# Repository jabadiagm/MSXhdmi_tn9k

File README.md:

# MSXhdmi_tn9k
Adaptador hdmi para MSX1

Permite conectar un MSX de primera generación a un monitor convencional. La lógica está contenida en una Tang Nano 9K que se encarga de reproducir imagen (vdp) y sonido (psg).

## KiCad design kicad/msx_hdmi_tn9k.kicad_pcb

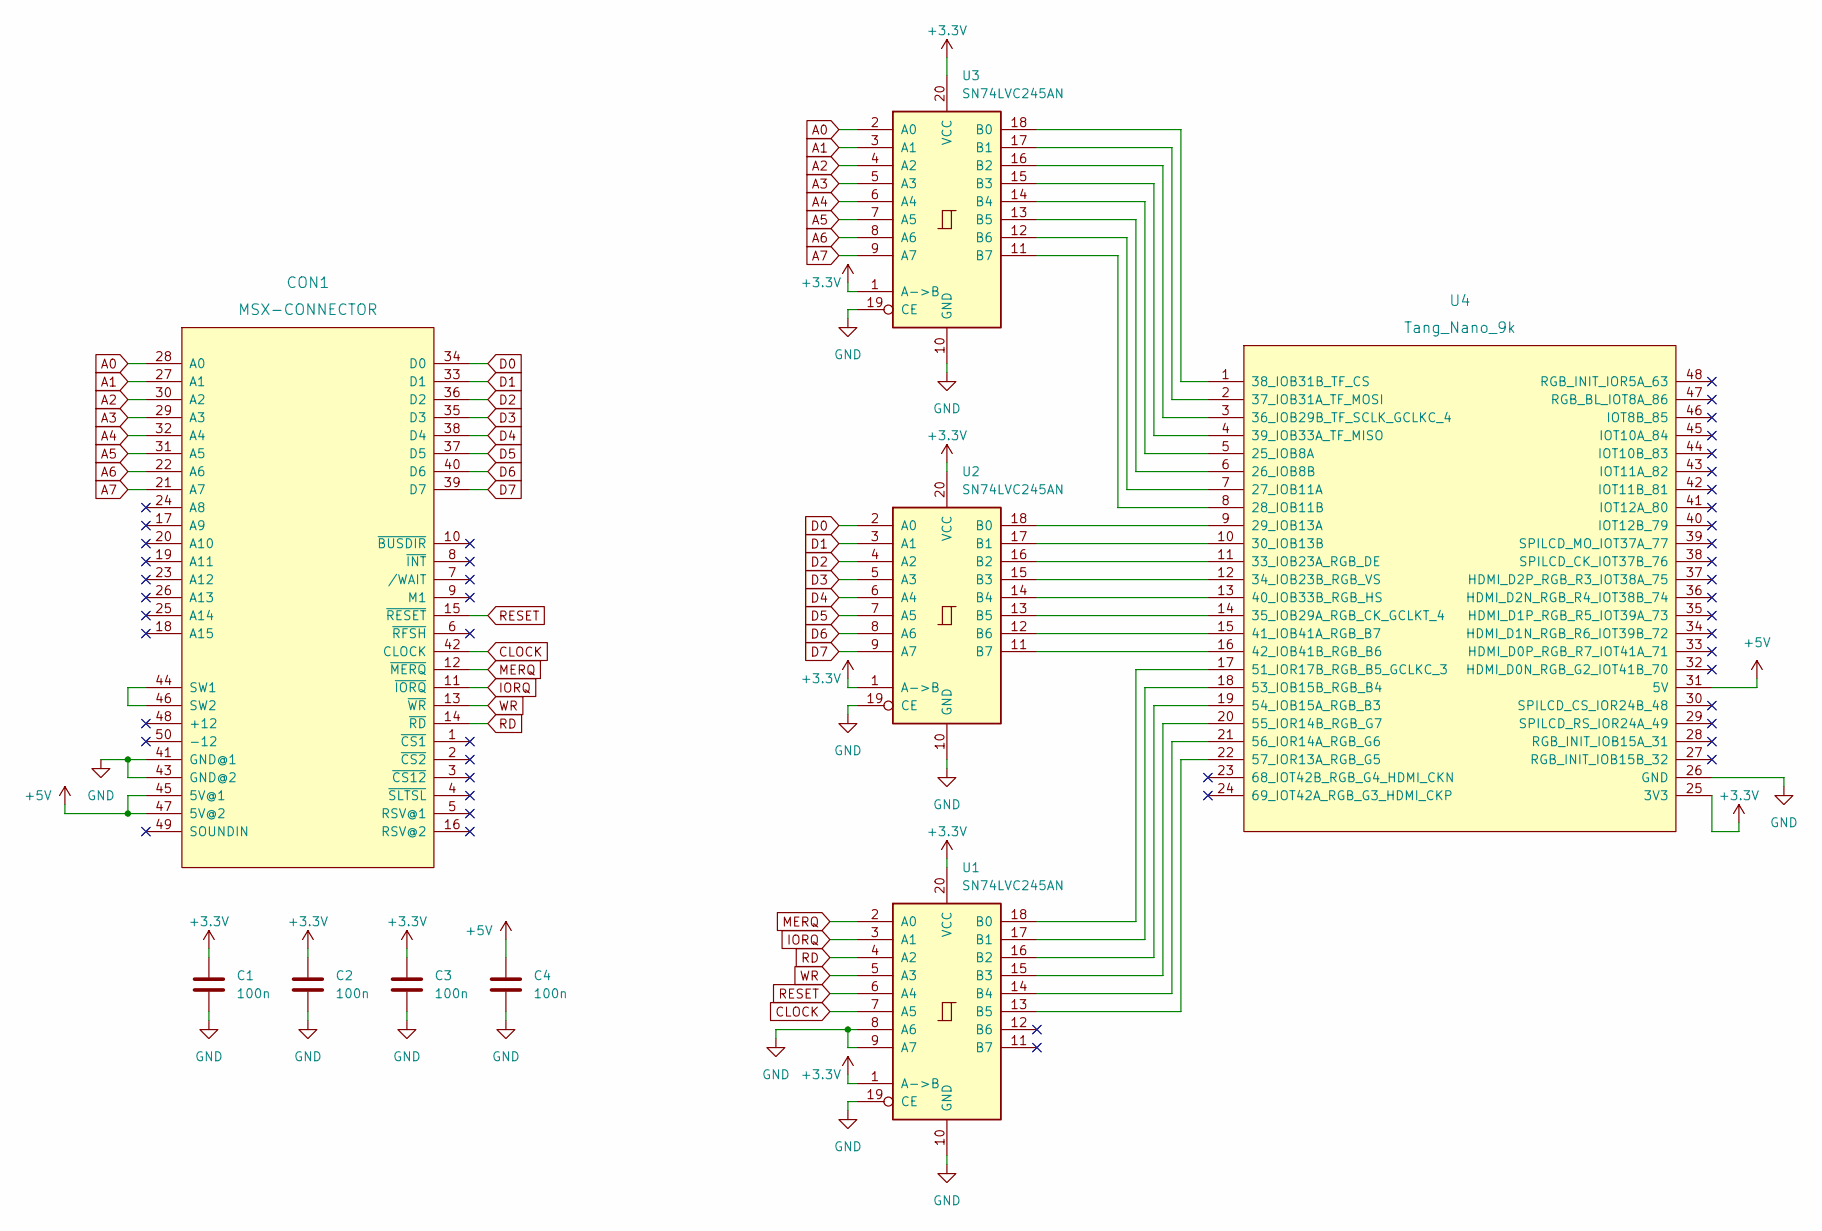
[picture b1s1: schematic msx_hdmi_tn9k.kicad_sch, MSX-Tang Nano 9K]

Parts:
C1, C2, C3, C4: 100n; C_Disc_D4.3mm_W1.9mm_P5.00mm
CON1: MSX-CONNECTOR; CARTRIDGE_MSX
U1, U2, U3: SN74LVC245AN; DIP-20_W7.62mm
U4: Tang_Nano_9k

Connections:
+3.3V: C1.1, C2.1, C3.1, U1.1 (A->B), U1.20 (VCC), U2.1 (A->B), U2.20 (VCC), U3.1 (A->B), U3.20 (VCC), U4.25 (3V3)
+5V: C4.1, CON1.45 (5V@1), CON1.47 (5V@2), U4.31 (5V)
A0: CON1.28 (A0), U3.2 (A0)
A1: CON1.27 (A1), U3.3 (A1)
A2: CON1.30 (A2), U3.4 (A2)
A3: CON1.29 (A3), U3.5 (A3)
A4: CON1.32 (A4), U3.6 (A4)
A5: CON1.31 (A5), U3.7 (A5)
A6: CON1.22 (A6), U3.8 (A6)
A7: CON1.21 (A7), U3.9 (A7)
CLOCK: CON1.42 (CLOCK), U1.7 (A5)
D0: CON1.34 (D0), U2.2 (A0)
D1: CON1.33 (D1), U2.3 (A1)
D2: CON1.36 (D2), U2.4 (A2)
D3: CON1.35 (D3), U2.5 (A3)
D4: CON1.38 (D4), U2.6 (A4)
D5: CON1.37 (D5), U2.7 (A5)
D6: CON1.40 (D6), U2.8 (A6)
D7: CON1.39 (D7), U2.9 (A7)
GND: C1.2, C2.2, C3.2, C4.2, CON1.41 (GND@1), CON1.43 (GND@2), U1.8 (A6), U1.9 (A7), U1.10 (GND), U1.19 (CE), U2.10 (GND), U2.19 (CE), U3.10 (GND), U3.19 (CE), U4.26 (GND)
IORQ: CON1.11 (~IORQ), U1.3 (A1)
MERQ: CON1.12 (~MERQ), U1.2 (A0)
unnamed: CON1.44 (SW1), CON1.46 (SW2)
unnamed: U1.13 (B5), U4.22 (57_IOR13A_RGB_G5)
unnamed: U1.14 (B4), U4.21 (56_IOR14A_RGB_G6)
unnamed: U1.15 (B3), U4.20 (55_IOR14B_RGB_G7)
unnamed: U1.16 (B2), U4.19 (54_IOB15A_RGB_B3)
unnamed: U1.17 (B1), U4.18 (53_IOB15B_RGB_B4)
unnamed: U1.18 (B0), U4.17 (51_IOR17B_RGB_B5_GCLKC_3)
unnamed: U2.11 (B7), U4.16 (42_IOB41B_RGB_B6)
unnamed: U2.12 (B6), U4.15 (41_IOB41A_RGB_B7)
unnamed: U2.13 (B5), U4.14 (35_IOB29A_RGB_CK_GCLKT_4)
unnamed: U2.14 (B4), U4.13 (40_IOB33B_RGB_HS)
unnamed: U2.15 (B3), U4.12 (34_IOB23B_RGB_VS)
unnamed: U2.16 (B2), U4.11 (33_IOB23A_RGB_DE)
unnamed: U2.17 (B1), U4.10 (30_IOB13B)
unnamed: U2.18 (B0), U4.9 (29_IOB13A)
unnamed: U3.11 (B7), U4.8 (28_IOB11B)
unnamed: U3.12 (B6), U4.7 (27_IOB11A)
unnamed: U3.13 (B5), U4.6 (26_IOB8B)
unnamed: U3.14 (B4), U4.5 (25_IOB8A)
unnamed: U3.15 (B3), U4.4 (39_IOB33A_TF_MISO)
unnamed: U3.16 (B2), U4.3 (36_IOB29B_TF_SCLK_GCLKC_4)
unnamed: U3.17 (B1), U4.2 (37_IOB31A_TF_MOSI)
unnamed: U3.18 (B0), U4.1 (38_IOB31B_TF_CS)
RD: CON1.14 (~RD), U1.4 (A2)
RESET: CON1.15 (~RESET), U1.6 (A4)
WR: CON1.13 (~WR), U1.5 (A3)

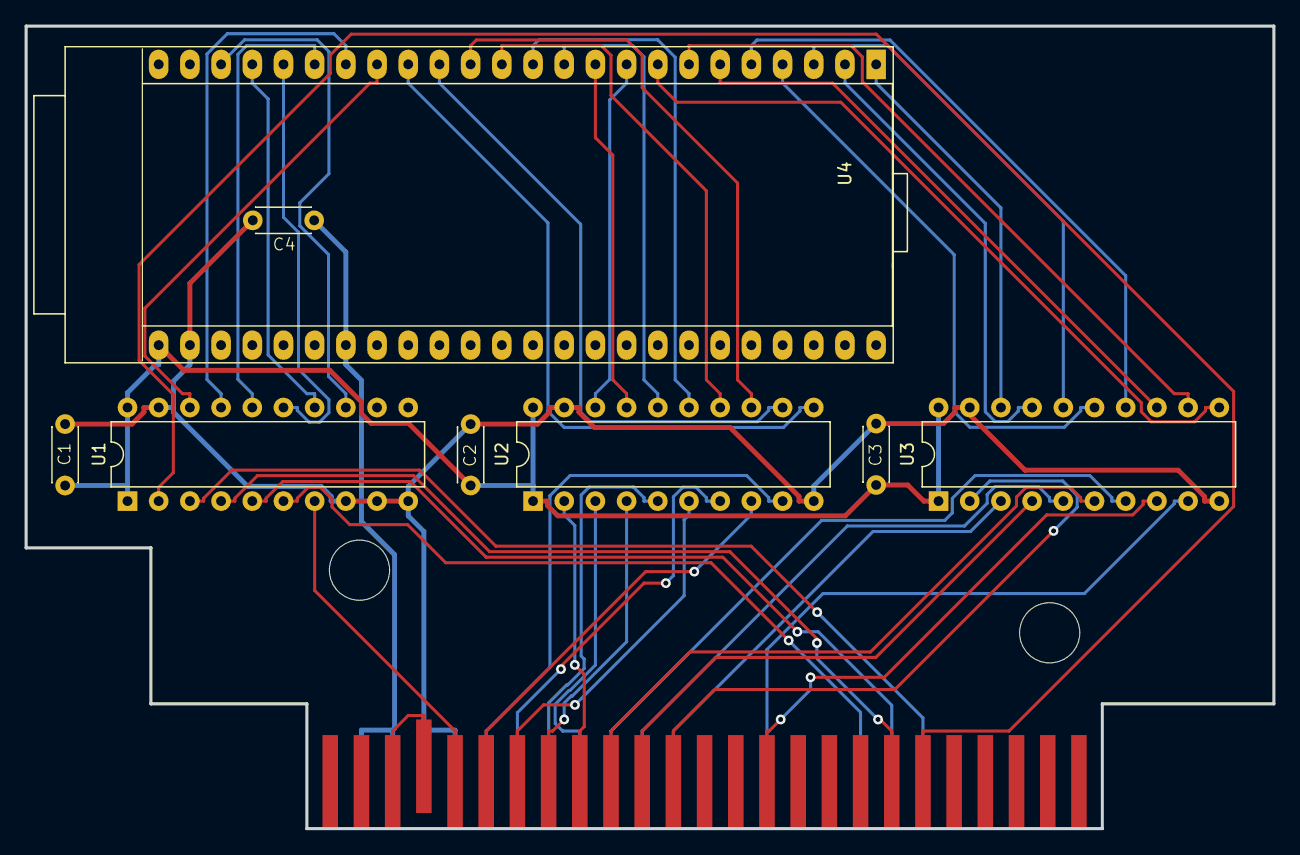
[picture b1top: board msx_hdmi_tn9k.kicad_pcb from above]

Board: 2 copper layers, 101.6 x 65.3 mm, 9 parts (0 on the bottom side), 48 nets.

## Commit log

2023-05-11 Previo
2023-05-20 Inicial
